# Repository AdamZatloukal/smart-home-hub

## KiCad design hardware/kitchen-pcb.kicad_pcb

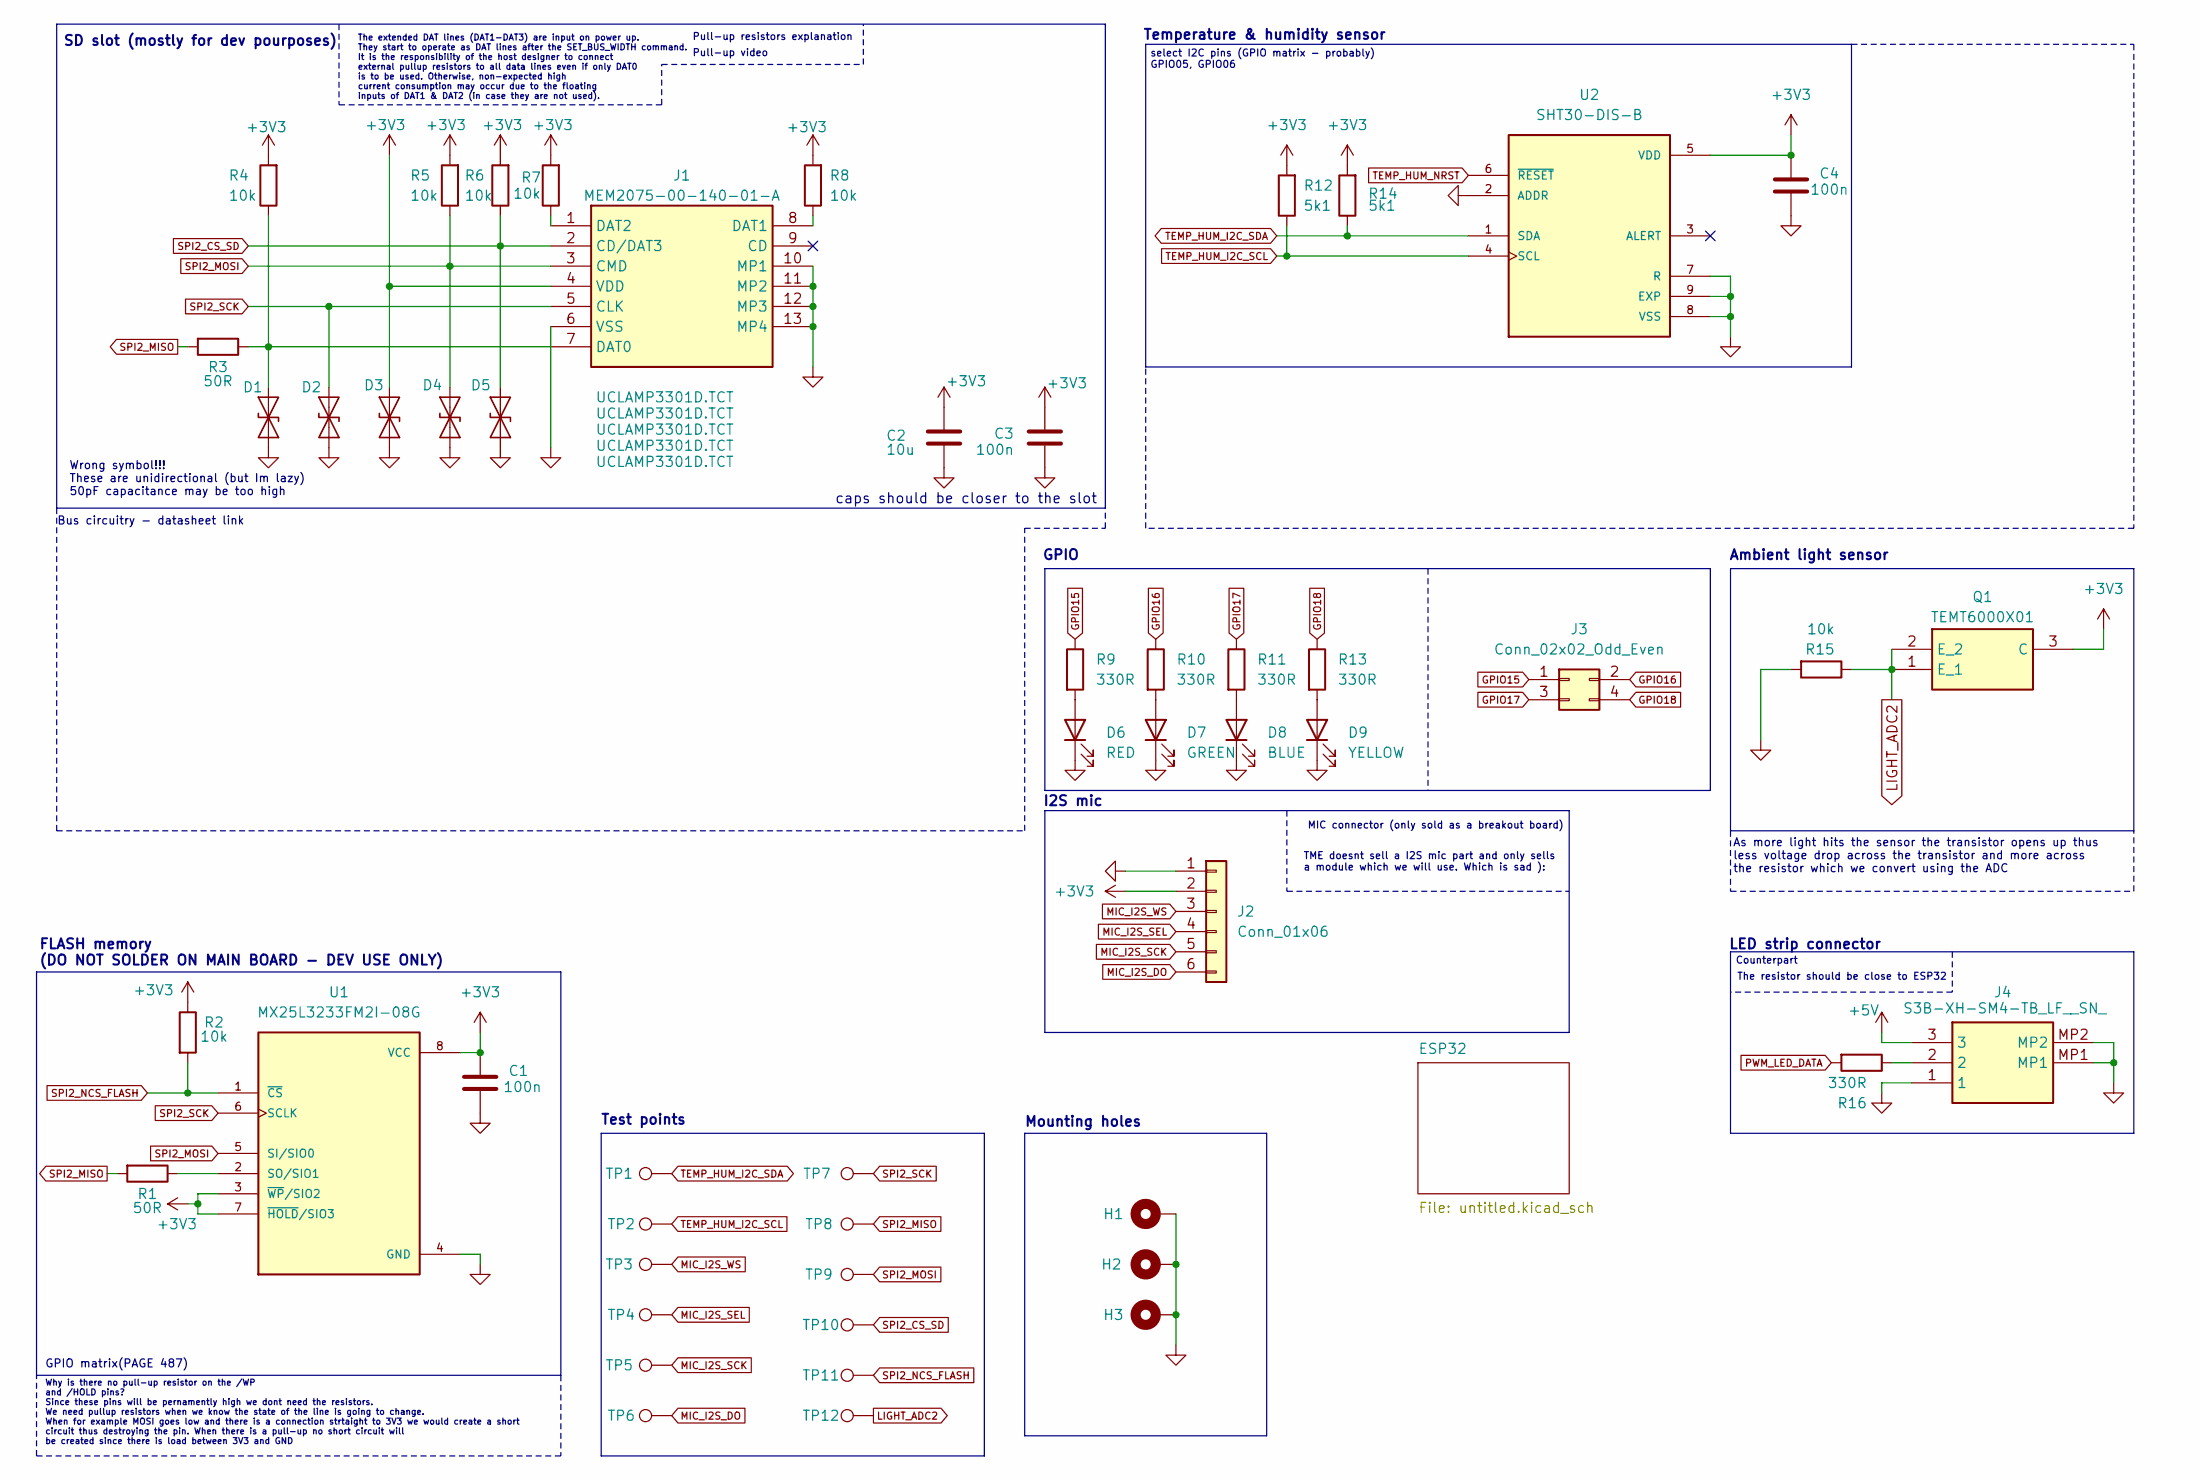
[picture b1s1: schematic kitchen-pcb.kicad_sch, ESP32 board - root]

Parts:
C1, C3, C4: 100n; C_0805_2012Metric_Pad1.18x1.45mm_HandSolder
C2: 10u; C_0805_2012Metric_Pad1.18x1.45mm_HandSolder
D1, D2, D3, D4, D5: UCLAMP3301D.TCT; SOD2512X110L
D6: RED; LED_0603_1608Metric_Pad1.05x0.95mm_HandSolder
D7: GREEN; LED_0603_1608Metric_Pad1.05x0.95mm_HandSolder
D8: BLUE; LED_0603_1608Metric_Pad1.05x0.95mm_HandSolder
D9: YELLOW; LED_0603_1608Metric_Pad1.05x0.95mm_HandSolder
H1, H2, H3: MountingHole_Pad; MountingHole_3.2mm_M3_DIN965_Pad_TopBottom
J1: MEM2075-00-140-01-A; MEM20750014001A; Manufacturer_Part_Number MEM2075-00-140-01-A
J2: Conn_01x06; mic-module
J3: Conn_02x02_Odd_Even; PinHeader_2x02_P2.54mm_Vertical
J4: S3B-XH-SM4-TB_LF__SN_; S3BXHSM4TBLFSN; Mouser Part Number N/A
Q1: TEMT6000X01; Manufacturer_Part_Number TEMT6000X01
R1, R3: 50R; R_0603_1608Metric_Pad0.98x0.95mm_HandSolder
R2, R4, R5, R6, R7, R8, R15: 10k; R_0805_2012Metric_Pad1.20x1.40mm_HandSolder
R9, R10, R11, R13, R16: 330R; R_0805_2012Metric_Pad1.20x1.40mm_HandSolder
R12, R14: 5k1; R_0805_2012Metric_Pad1.20x1.40mm_HandSolder
TP1, TP3, TP7: Test_SCK; TestPoint_Pad_D1.0mm
TP2, TP4, TP8: Test_MISO; TestPoint_Pad_D1.0mm
TP5, TP9: Test_MOSI; TestPoint_Pad_D1.0mm
TP6, TP10: Test_CS_SD; TestPoint_Pad_D1.0mm
TP11, TP12: Test_NCS_FLASH; TestPoint_Pad_D1.0mm
U1: MX25L3233FM2I-08G; SOIC127P790X216-8N_MX25L3233FM2I-08G; PARTREV 1.6
U2: SHT30-DIS-B; DFN250X250X100-9N

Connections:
+3V3: C1.2, C2.1, C3.1, C4.2, D3.2 (A2), J1.4 (VDD), J2.2, Q1.3 (C), R2.1, R4.2, R5.2, R6.2, R7.2, R8.2, R12.2, R14.2, U1.3 (~WP/SIO2), U1.7 (~HOLD/SIO3), U1.8 (VCC), U2.5 (VDD); also elsewhere on the board
+5V: J4.3; also elsewhere on the board
GND: C1.1, C2.2, C3.2, C4.1, D1.1 (A1), D2.1 (A1), D3.1 (A1), D4.1 (A1), D5.1 (A1), D6.1 (K), D7.1 (K), D8.1 (K), D9.1 (K), H1.1, H2.1, H3.1, J1.6 (VSS), J1.10 (MP1), J1.11 (MP2), J1.12 (MP3), J1.13 (MP4), J2.1, J4.1, J4.MP1, J4.MP2, R15.2, U1.4 (GND), U2.2 (ADDR), U2.7 (R), U2.8 (VSS), U2.9 (EXP); also elsewhere on the board
GPIO15: J3.1, R9.1; also elsewhere on the board
GPIO16: J3.2, R10.1; also elsewhere on the board
GPIO17: J3.3, R11.1; also elsewhere on the board
GPIO18: J3.4, R13.1; also elsewhere on the board
LIGHT_ADC2: Q1.1 (E_1), Q1.2 (E_2), R15.1, TP12.1; also elsewhere on the board
MIC_I2S_DO: J2.6, TP6.1; also elsewhere on the board
MIC_I2S_SCK: J2.5, TP5.1; also elsewhere on the board
MIC_I2S_SEL: J2.4, TP4.1; also elsewhere on the board
MIC_I2S_WS: J2.3, TP3.1; also elsewhere on the board
unnamed: D1.2 (A2), J1.7 (DAT0), R3.1, R4.1
unnamed: D6.2 (A), R9.2
unnamed: D7.2 (A), R10.2
unnamed: D8.2 (A), R11.2
unnamed: D9.2 (A), R13.2
unnamed: J1.8 (DAT1), R8.1
unnamed: J1.1 (DAT2), R7.1
unnamed: J4.2, R16.1
unnamed: R1.1, U1.2 (SO/SIO1)
PWM_LED_DATA: R16.2; also elsewhere on the board
SPI2_CS_SD: D5.2 (A2), J1.2 (CD/DAT3), R6.1, TP10.1; also elsewhere on the board
SPI2_MISO: R1.2, R3.2, TP8.1; also elsewhere on the board
SPI2_MOSI: D4.2 (A2), J1.3 (CMD), R5.1, TP9.1, U1.5 (SI/SIO0); also elsewhere on the board
SPI2_NCS_FLASH: R2.2, TP11.1, U1.1 (~CS); also elsewhere on the board
SPI2_SCK: D2.2 (A2), J1.5 (CLK), TP7.1, U1.6 (SCLK); also elsewhere on the board
TEMP_HUM_I2C_SCL: R12.1, TP2.1, U2.4 (SCL); also elsewhere on the board
TEMP_HUM_I2C_SDA: R14.1, TP1.1, U2.1 (SDA); also elsewhere on the board
TEMP_HUM_NRST: U2.6 (~RESET); also elsewhere on the board

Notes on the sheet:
Pull-up resistors explanation
As more light hits the sensor the transistor opens up thus less voltage drop across the transistor and more across the resistor which we convert using the ADC
Ambient light sensor
Mounting holes
MIC connector (only sold as a breakout board)
Counterpart
caps should be closer to the slot
Bus circuitry - datasheet link
Why is there no pull-up resistor on the /WP and /HOLD pins? Since these pins will be pernamently high we dont need the resistors. We need pullup resistors when we know the state of the line is going to change. When for example MOSI goes low and there is a connection strtaight to 3V3 we would create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
Wrong symbol!!! These are unidirectional (but Im lazy) 50pF capacitance may be too high
GPIO matrix(PAGE 487)
Pull-up video
GPIO
FLASH memory (DO NOT SOLDER ON MAIN BOARD - DEV USE ONLY)
SD slot (mostly for dev pourposes)
LED strip connector
TME doesnt sell a I2S mic part and only sells a module which we will use. Which is sad ):
Test points
The extended DAT lines (DAT1-DAT3) are input on power up. They start to operate as DAT lines after the SET_BUS_WIDTH command. It is the responsibility of the host designer to connect external pullup resistors to all data lines even if only DAT0 is to be used. Otherwise, non-expected high current co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
Temperature & humidity sensor
I2S mic
The resistor should be close to ESP32
select I2C pins (GPIO matrix - probably) GPIO05, GPIO06

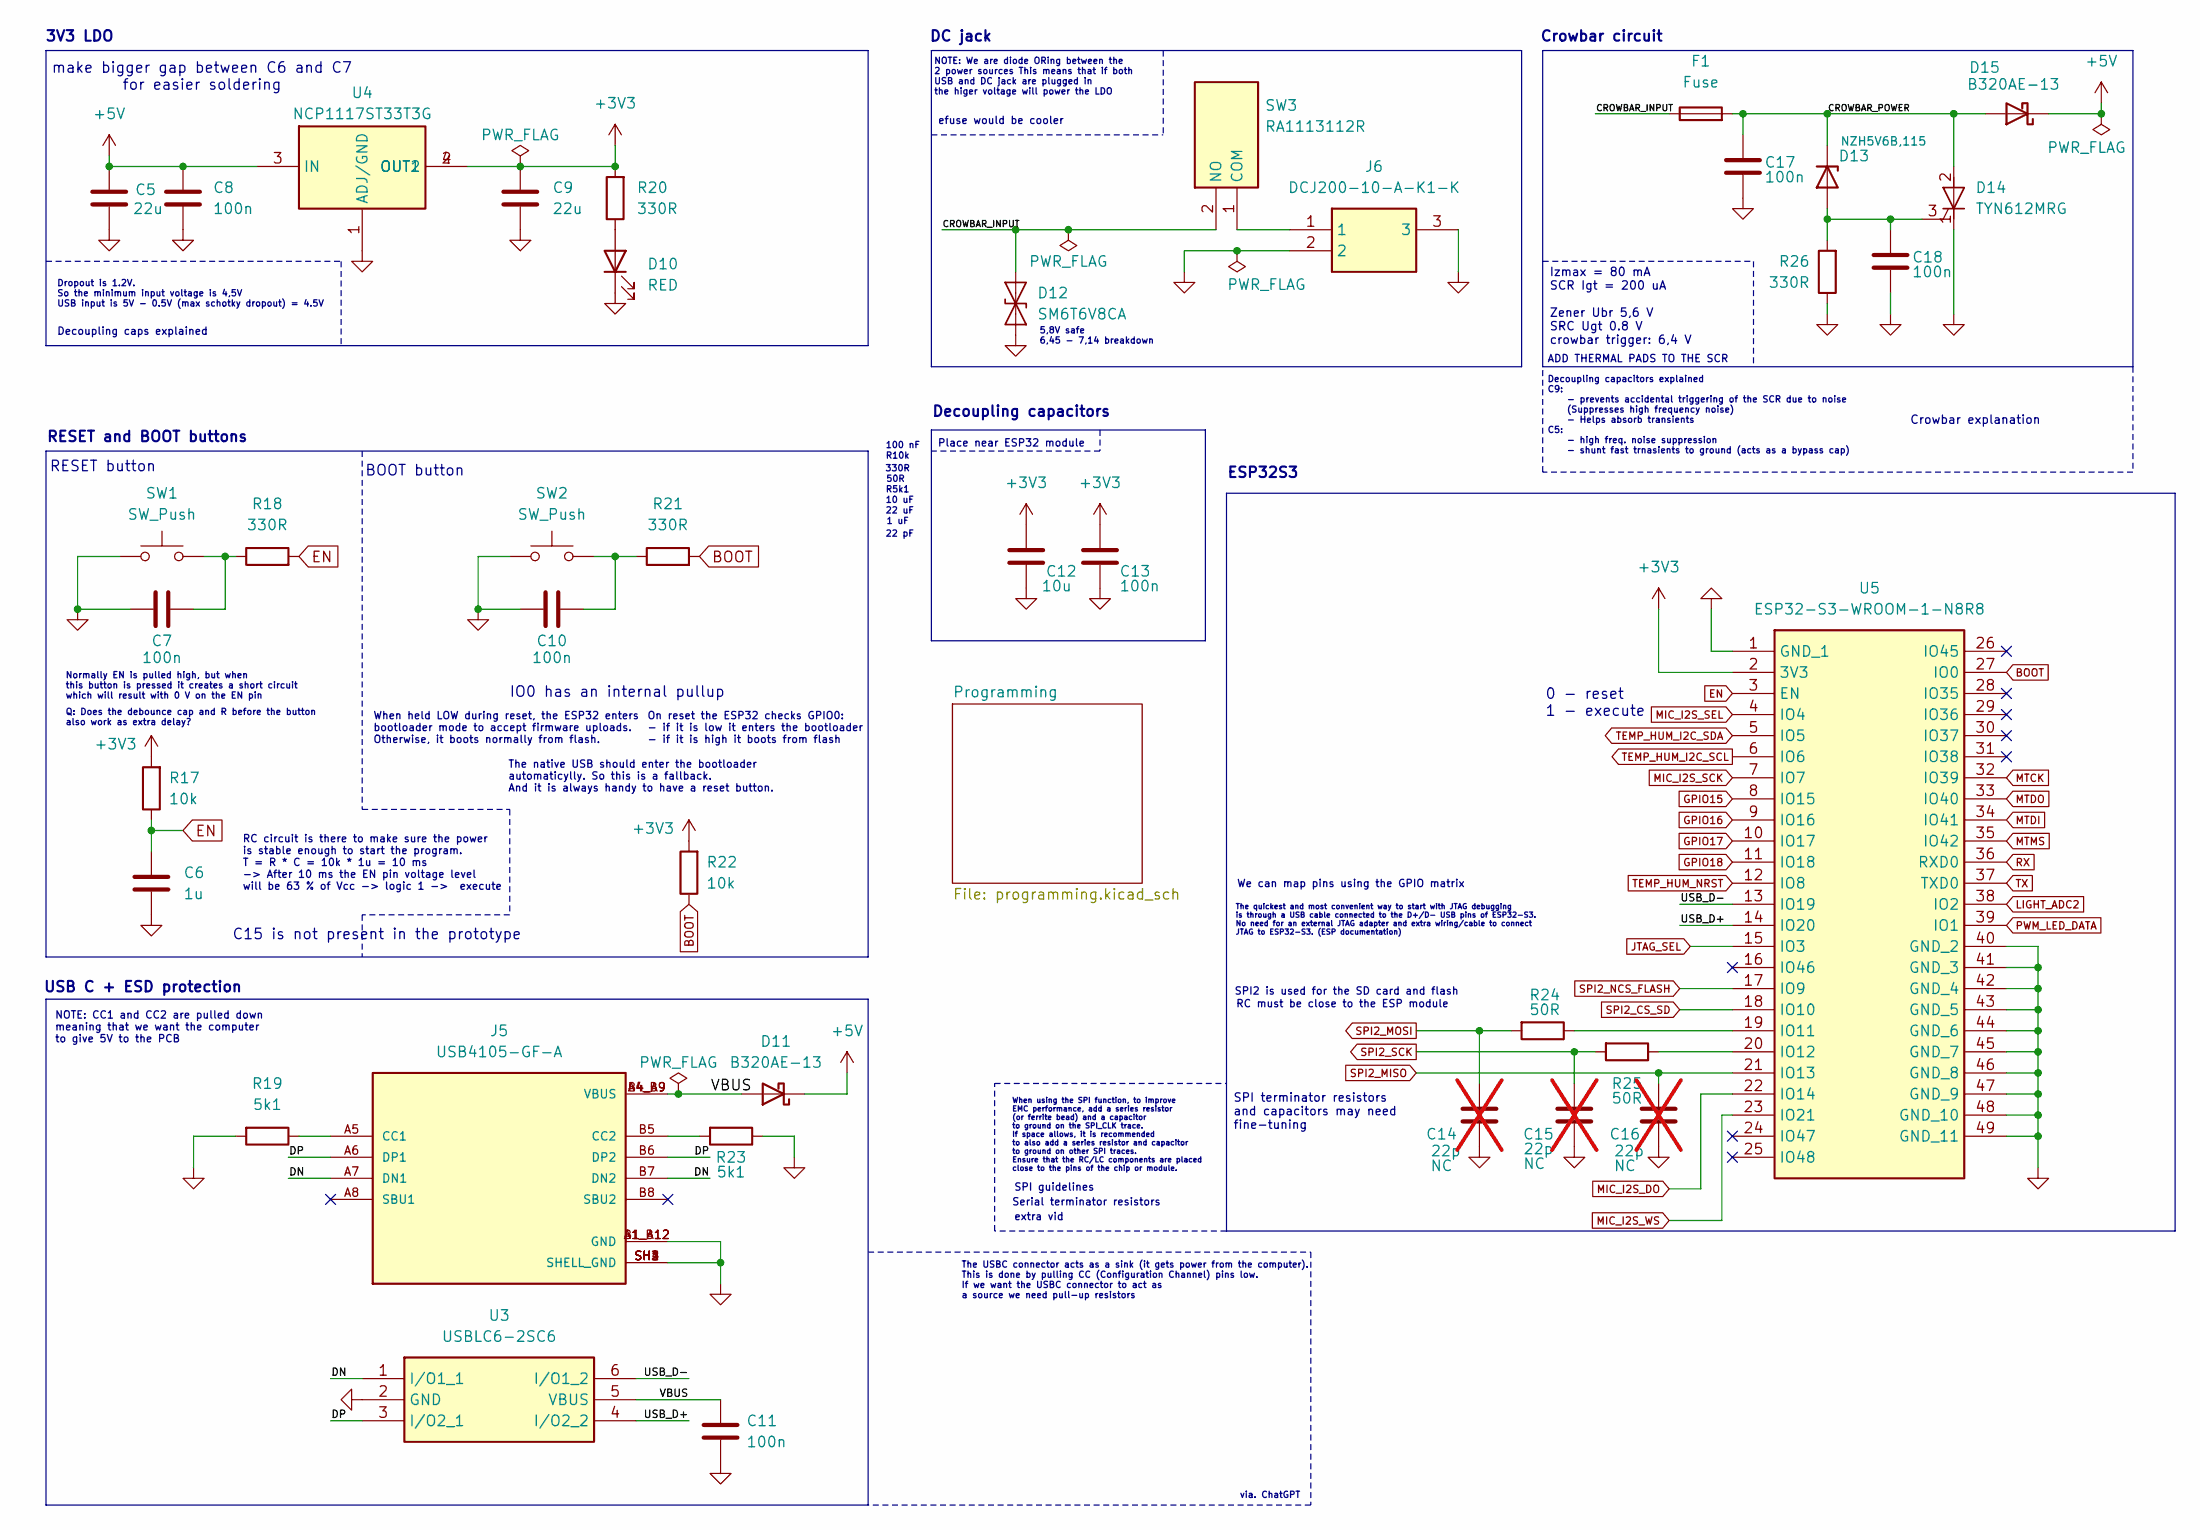
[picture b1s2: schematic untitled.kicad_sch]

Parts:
C5, C9: 22u; C_0805_2012Metric_Pad1.18x1.45mm_HandSolder
C6: 1u; C_0805_2012Metric_Pad1.18x1.45mm_HandSolder
C7, C8, C10, C11, C13, C17, C18: 100n; C_0805_2012Metric_Pad1.18x1.45mm_HandSolder
C12: 10u; C_0805_2012Metric_Pad1.18x1.45mm_HandSolder
C14, C15, C16: 22p; C_0805_2012Metric_Pad1.18x1.45mm_HandSolder; not fitted
D10: RED; LED_0603_1608Metric_Pad1.05x0.95mm_HandSolder
D11: B320AE-13; DIONM5226X230N
D12: SM6T6V8CA; DIONM5436X265N
D13: NZH5V6B,115; D_SOD-123F
D14: TYN612MRG; TS820600B
D15: B320AE-13; D_SMA
F1: Fuse; FUSC6125X279N
J5: USB4105-GF-A; GCT_USB4105-GF-A; PARTREV B4
J6: DCJ200-10-A-K1-K; BarrelJack_GCT_DCJ200-10-A_Horizontal; Manufacturer_Part_Number DCJ200-10-A-K1-K
R17, R22: 10k; R_0805_2012Metric_Pad1.20x1.40mm_HandSolder
R18, R20, R21, R26: 330R; R_0805_2012Metric_Pad1.20x1.40mm_HandSolder
R19, R23: 5k1; R_0805_2012Metric_Pad1.20x1.40mm_HandSolder
R24, R25: 50R; R_0402_1005Metric_Pad0.72x0.64mm_HandSolder
SW1, SW2: SW_Push; SW_PUSH_6mm_H9.5mm
SW3: RA1113112R; Manufacturer_Part_Number R1966ABLKBLKGR
U3: USBLC6-2SC6; SOT95P280X145-6N; Manufacturer_Part_Number USBLC6-2SC6
U4: NCP1117ST33T3G; SOT230P700X180-4N
U5: ESP32-S3-WROOM-1-N8R8; ESP32S3WROOM1N4; Manufacturer_Part_Number ESP32-S3-WROOM-1-N8R8

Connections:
+3V3: C9.1, C12.1, C13.1, R17.2, R20.2, R22.2, U4.2 (OUT1), U4.4 (OUT2), U5.2 (3V3); also elsewhere on the board
+5V: C5.1, C8.1, D11.1 (K), D15.1 (K), U4.3 (IN); also elsewhere on the board
/ESP32/CROWBAR_INPUT: D12.2 (A2), F1.1, SW3.2 (NO)
/ESP32/CROWBAR_POWER: C17.1, D13.1 (K), D14.2 (A), D15.2 (A), F1.2
/ESP32/DN: J5.A7 (DN1), J5.B7 (DN2), U3.1 (I/O1_1)
/ESP32/DP: J5.A6 (DP1), J5.B6 (DP2), U3.3 (I/O2_1)
/ESP32/USB_D+: U3.4 (I/O2_2), U5.14 (IO20)
/ESP32/USB_D-: U3.6 (I/O1_2), U5.13 (IO19)
/ESP32/VBUS: C11.1, D11.2 (A), J5.A4_B9 (VBUS), J5.B4_A9 (VBUS), U3.5 (VBUS)
BOOT: R21.2, R22.1, U5.27 (IO0); also elsewhere on the board
EN: C6.2, R17.1, R18.2, U5.3 (EN); also elsewhere on the board
GND: C5.2, C6.1, C7.1, C8.2, C9.2, C10.1, C11.2, C12.2, C13.2, C14.1, C15.1, C16.1, C17.2, C18.2, D10.1 (K), D12.1 (A1), D14.1 (K), J5.A1_B12 (GND), J5.B1_A12 (GND), J5.SH1 (SHELL_GND), J5.SH2 (SHELL_GND), J5.SH3 (SHELL_GND), J5.SH4 (SHELL_GND), J6.2, J6.3, R19.2, R23.1, R26.1, SW1.1, SW2.1, U3.2 (GND), U4.1 (ADJ/GND), U5.1 (GND_1), U5.40 (GND_2), U5.41 (GND_3), U5.42 (GND_4), U5.43 (GND_5), U5.44 (GND_6), U5.45 (GND_7), U5.46 (GND_8), U5.47 (GND_9), U5.48 (GND_10), U5.49 (GND_11); also elsewhere on the board
GPIO15: U5.8 (IO15); also elsewhere on the board
GPIO16: U5.9 (IO16); also elsewhere on the board
GPIO17: U5.10 (IO17); also elsewhere on the board
GPIO18: U5.11 (IO18); also elsewhere on the board
JTAG_SEL: U5.15 (IO3); also elsewhere on the board
LIGHT_ADC2: U5.38 (IO2); also elsewhere on the board
MIC_I2S_DO: U5.22 (IO14); also elsewhere on the board
MIC_I2S_SCK: U5.7 (IO7); also elsewhere on the board
MIC_I2S_SEL: U5.4 (IO4); also elsewhere on the board
MIC_I2S_WS: U5.23 (IO21); also elsewhere on the board
MTCK: U5.32 (IO39); also elsewhere on the board
MTDI: U5.34 (IO41); also elsewhere on the board
MTDO: U5.33 (IO40); also elsewhere on the board
MTMS: U5.35 (IO42); also elsewhere on the board
unnamed: C7.2, R18.1, SW1.2
unnamed: C10.2, R21.1, SW2.2
unnamed: D10.2 (A), R20.1
unnamed: C18.1, D13.2 (A), D14.3 (G), R26.2
unnamed: J5.A5 (CC1), R19.1
unnamed: J5.B5 (CC2), R23.2
unnamed: J6.1, SW3.1 (COM)
unnamed: R24.1, U5.19 (IO11)
unnamed: R25.1, U5.20 (IO12)
PWM_LED_DATA: U5.39 (IO1); also elsewhere on the board
RX: U5.36 (RXD0); also elsewhere on the board
SPI2_CS_SD: U5.18 (IO10); also elsewhere on the board
SPI2_MISO: C16.2, U5.21 (IO13); also elsewhere on the board
SPI2_MOSI: C14.2, R24.2; also elsewhere on the board
SPI2_NCS_FLASH: U5.17 (IO9); also elsewhere on the board
SPI2_SCK: C15.2, R25.2; also elsewhere on the board
TEMP_HUM_I2C_SCL: U5.6 (IO6); also elsewhere on the board
TEMP_HUM_I2C_SDA: U5.5 (IO5); also elsewhere on the board
TEMP_HUM_NRST: U5.12 (IO8); also elsewhere on the board
TX: U5.37 (TXD0); also elsewhere on the board

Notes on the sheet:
330R
Q: Does the debounce cap and R before the button also work as extra delay?
DC jack
USB C + ESD protection
3V3 LDO
NOTE: CC1 and CC2 are pulled down meaning that we want the computer to give 5V to the PCB
Crowbar explanation
Serial terminator resistors
R5k1
22 uF
Decoupling capacitors explained C9: - prevents accidental triggering of the SCR due to noise (Suppresses high frequency noise) - Helps absorb transients C5: - high freq. noise suppression - shunt fast trnasients to ground (acts as a bypass cap)
R10k
SPI terminator resistors and capacitors may need fine-tuning
We can map pins using the GPIO matrix
0 - reset 1 - execute
ADD THERMAL PADS TO THE SCR
100 nF
RESET button
When held LOW during reset, the ESP32 enters bootloader mode to accept firmware uploads. Otherwise, it boots normally from flash.
SPI guidelines
IO0 has an internal pullup
make bigger gap between C6 and C7 for easier soldering
The USBC connector acts as a sink (it gets power from the computer). This is done by pulling CC (Configuration Channel) pins low. If we want the USBC connector to act as a source we need pull-up resistors
Decoupling caps explained
Izmax = 80 mA SCR Igt = 200 uA Zener Ubr 5,6 V SRC Ugt 0.8 V crowbar trigger: 6,4 V
Place near ESP32 module
50R
The quickest and most convenient way to start with JTAG debugging is through a USB cable connected to the D+/D- USB pins of ESP32-S3. No need for an external JTAG adapter and extra wiring/cable to connect JTAG to ESP32-S3. (ESP documentation)
extra vid
Crowbar circuit
efuse would be cooler
Dropout is 1.2V. So the minimum input voltage is 4,5V USB input is 5V - 0.5V (max schotky dropout) = 4.5V
RESET and BOOT buttons
22 pF
10 uF
via. ChatGPT
SPI2 is used for the SD card and flash
Decoupling capacitors
RC circuit is there to make sure the power is stable enough to start the program. T = R * C = 10k * 1u = 10 ms -> After 10 ms the EN pin voltage level will be 63 % of Vcc -> logic 1 -> execute
5,8V safe 6,45 - 7,14 breakdown

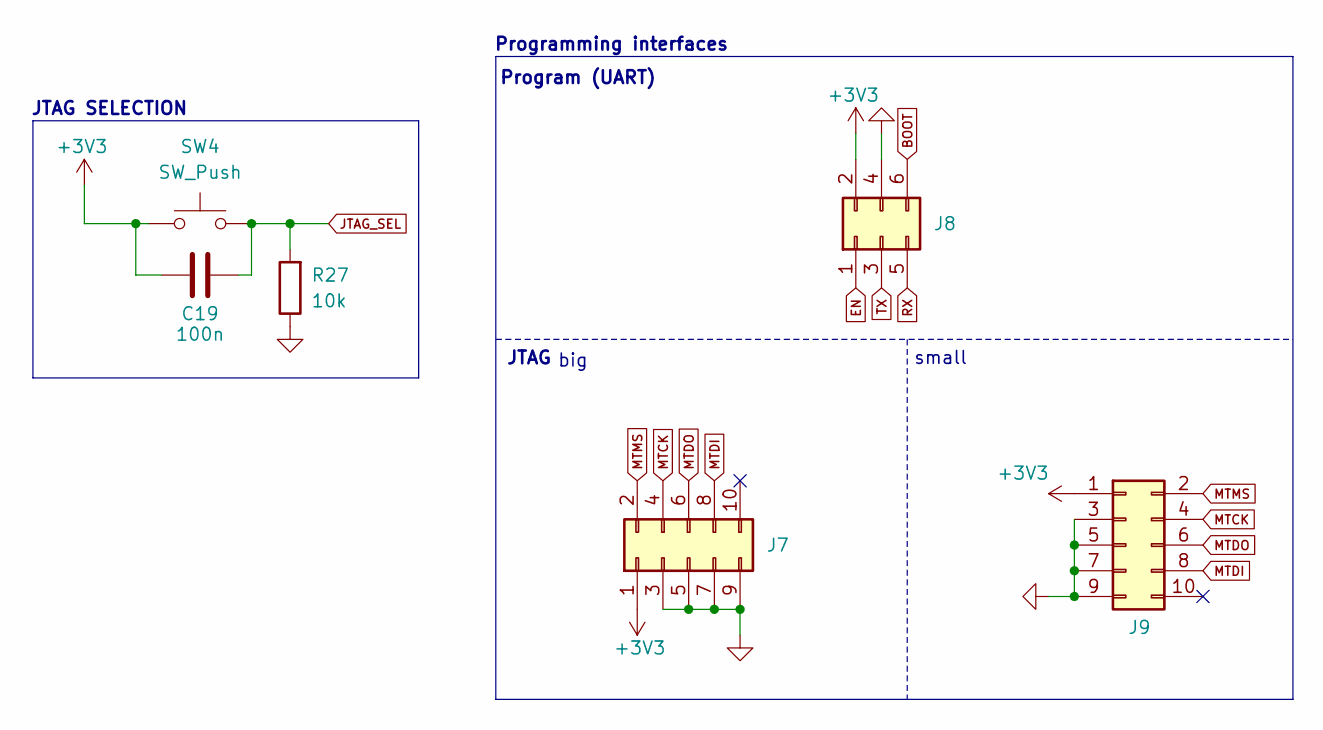
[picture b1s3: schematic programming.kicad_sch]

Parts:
C19: 100n; C_0805_2012Metric_Pad1.18x1.45mm_HandSolder
J7: Conn_02x05_Odd_Even; PinHeader_2x05_P2.54mm_Vertical
J8: Conn_02x03_Odd_Even; PinHeader_2x03_P2.54mm_Vertical
J9: Conn_02x05_Odd_Even; FTSH10501LDVK
R27: 10k; R_0805_2012Metric_Pad1.20x1.40mm_HandSolder
SW4: SW_Push; SW_PUSH_6mm_H9.5mm

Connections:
+3V3: C19.1, J7.1, J8.2, J9.1, SW4.1; also elsewhere on the board
BOOT: J8.6; also elsewhere on the board
EN: J8.1; also elsewhere on the board
GND: J7.3, J7.5, J7.7, J7.9, J8.4, J9.3, J9.5, J9.7, J9.9, R27.1; also elsewhere on the board
JTAG_SEL: C19.2, R27.2, SW4.2; also elsewhere on the board
MTCK: J7.4, J9.4; also elsewhere on the board
MTDI: J7.8, J9.8; also elsewhere on the board
MTDO: J7.6, J9.6; also elsewhere on the board
MTMS: J7.2, J9.2; also elsewhere on the board
RX: J8.5; also elsewhere on the board
TX: J8.3; also elsewhere on the board

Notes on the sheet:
JTAG
big
Programming interfaces
Program (UART)
small
JTAG SELECTION

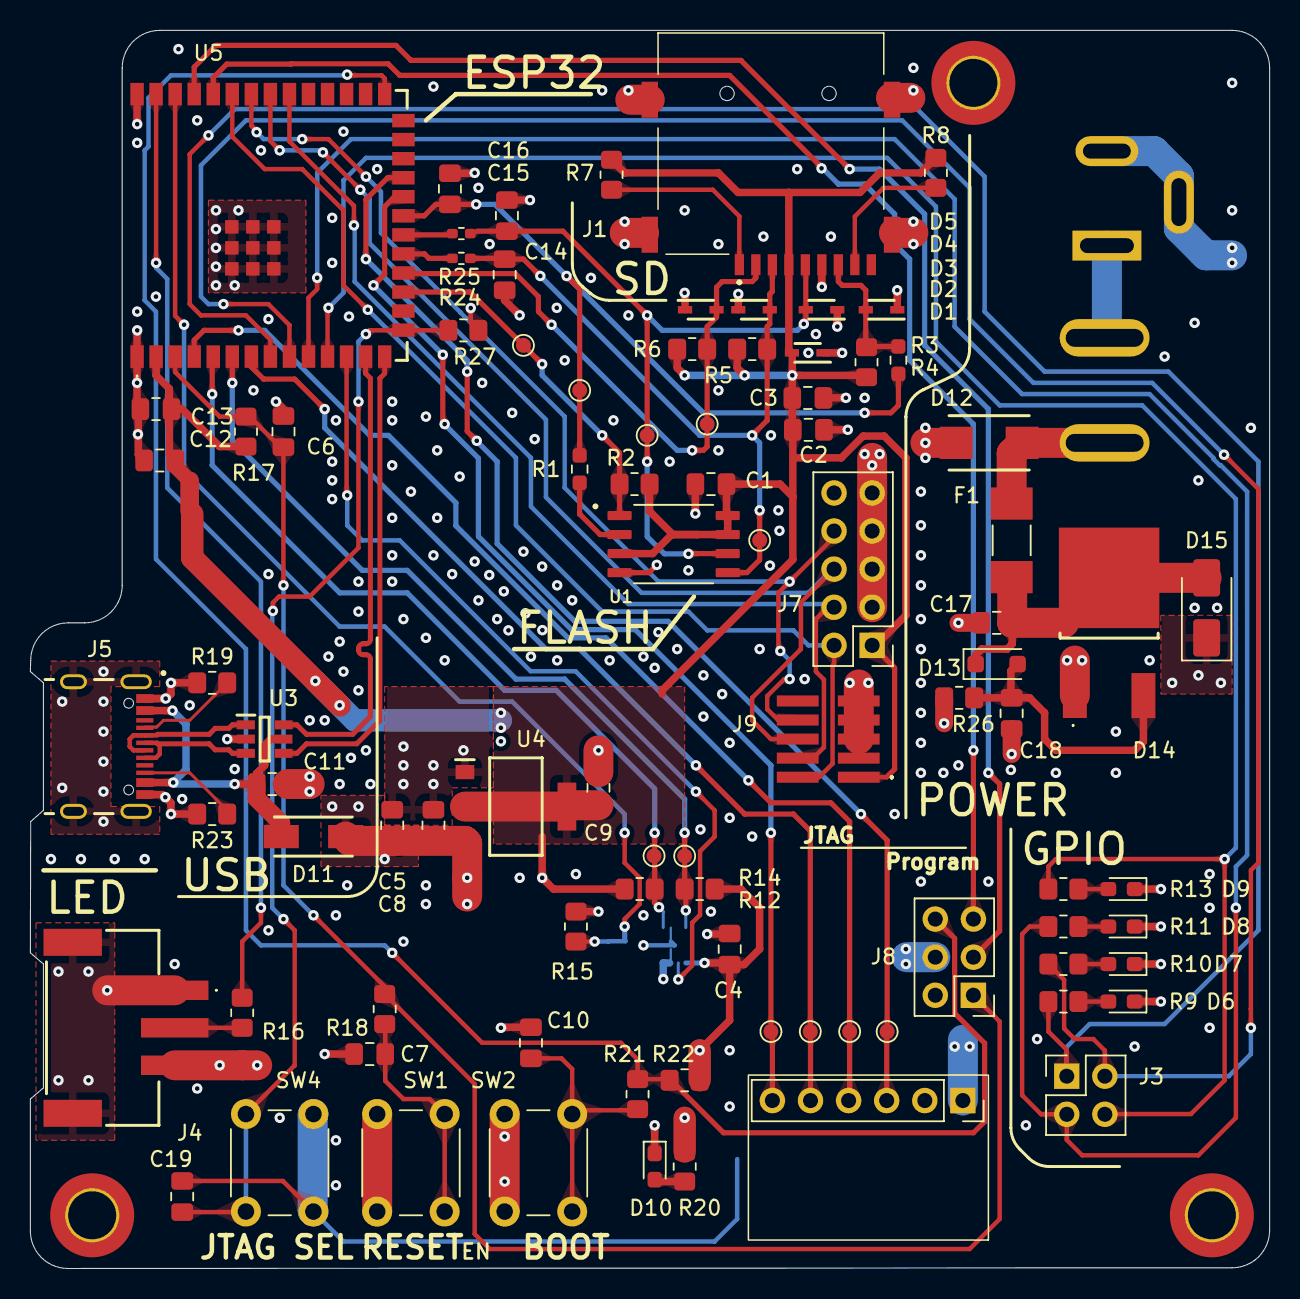
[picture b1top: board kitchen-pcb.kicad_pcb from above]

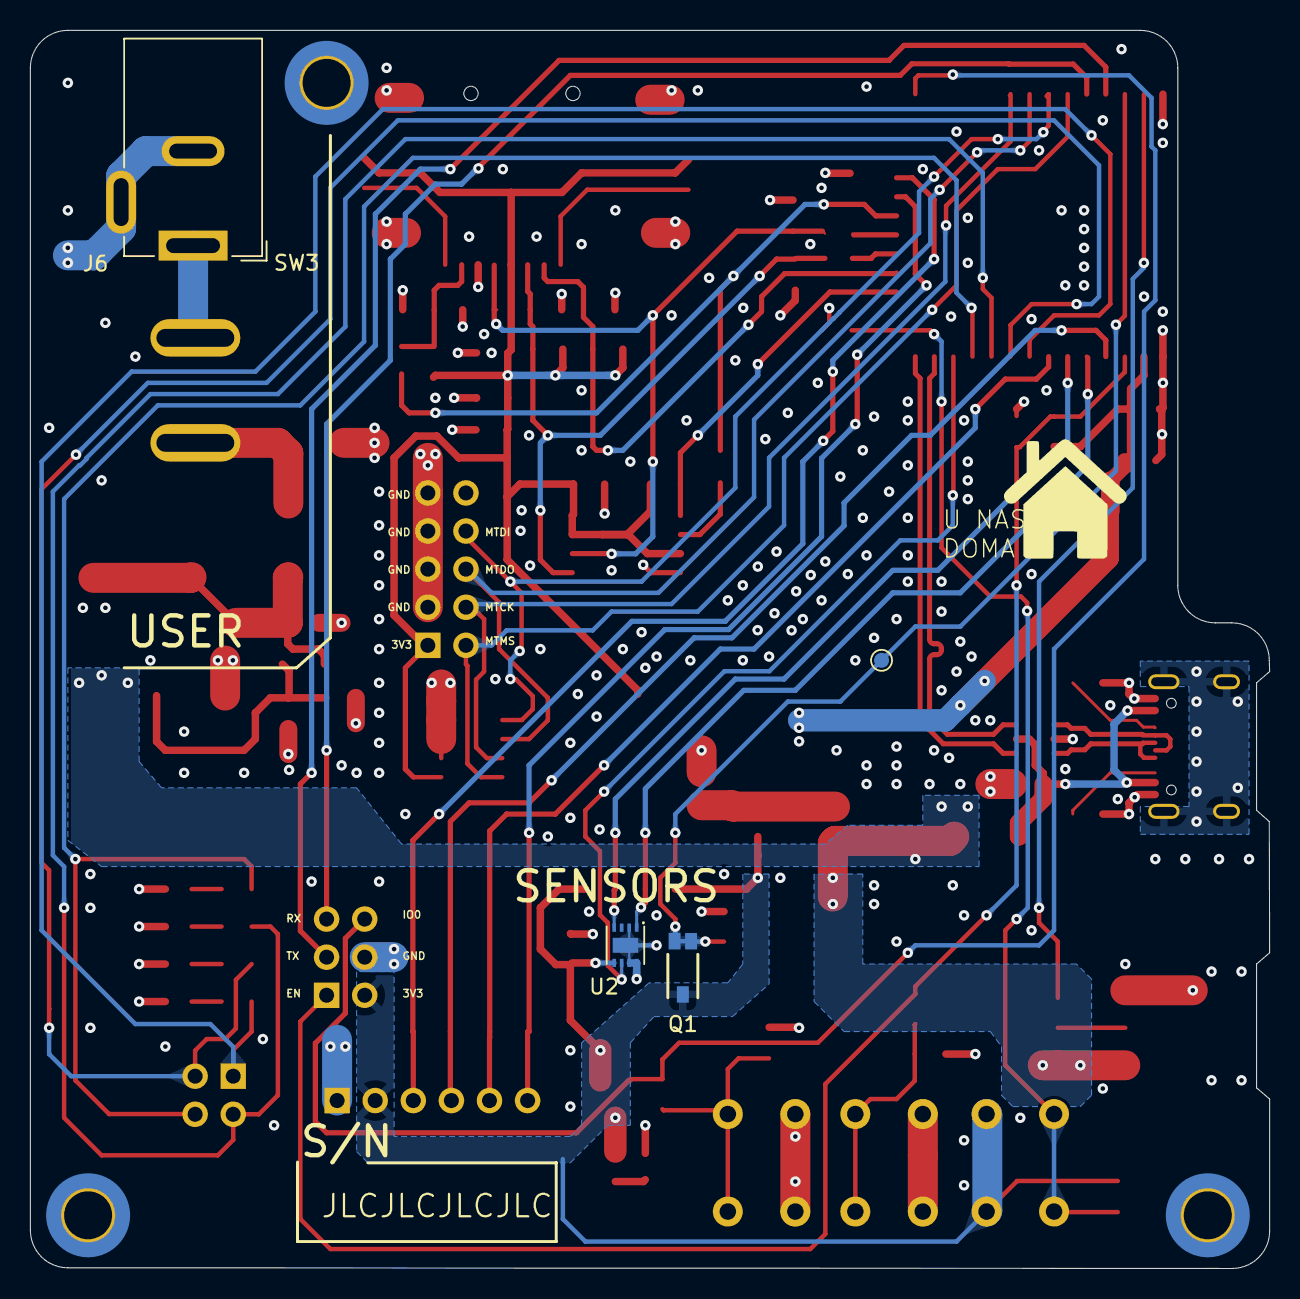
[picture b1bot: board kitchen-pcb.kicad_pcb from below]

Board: 4 copper layers, 82.6 x 82.5 mm, 96 parts (5 on the bottom side), 55 nets.

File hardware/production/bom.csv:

Designator,Footprint,Quantity,Value,LCSC Part #
"C1, C10, C11, C13, C17, C18, C19, C3, C4, C7, C8",0805,11,100n,
"C12, C2",0805,2,10u,
"C14, C15, C16",0805,3,22p,
"C5, C9",0805,2,22u,
C6,0805,1,1u,
"D1, D2, D3, D4, D5",SOD2512X110L,5,UCLAMP3301D.TCT,
"D10, D6",0603,2,RED,
D11,DIONM5226X230N,1,B320AE-13,
D12,DIONM5436X265N,1,SM6T6V8CA,
D13,D_SOD-123F,1,"NZH5V6B,115",
D14,TS820600B,1,TYN612MRG,
D15,D_SMA,1,B320AE-13,
D7,0603,1,GREEN,
D8,0603,1,BLUE,
D9,0603,1,YELLOW,
F1,FUSC6125X279N,1,Fuse,
J1,MEM20750014001A,1,MEM2075-00-140-01-A,
J2,mic-module,1,Conn_01x06,
J3,PinHeader_2x02_P2.54mm_Vertical,1,Conn_02x02_Odd_Even,
J4,S3BXHSM4TBLFSN,1,S3B-XH-SM4-TB_LF__SN_,
J5,GCT_USB4105-GF-A,1,USB4105-GF-A,
J6,BarrelJack_GCT_DCJ200-10-A_Horizontal,1,DCJ200-10-A-K1-K,
J7,PinHeader_2x05_P2.54mm_Vertical,1,Conn_02x05_Odd_Even,
J8,PinHeader_2x03_P2.54mm_Vertical,1,Conn_02x03_Odd_Even,
J9,FTSH10501LDVK,1,Conn_02x05_Odd_Even,
Q1,TEMT6000X01,1,TEMT6000X01,
"R1, R3",0603,2,50R,
"R10, R11, R13, R16, R18, R20, R21, R26, R9",0805,9,330R,
"R12, R14, R19, R23",0805,4,5k1,
"R15, R17, R2, R22, R27, R4, R5, R6, R7, R8",0805,10,10k,
"R24, R25",0402,2,50R,
"SW1, SW2, SW4",SW_PUSH_6mm_H9.5mm,3,SW_Push,
SW3,RA1113112R,1,RA1113112R,
"TP1, TP3, TP7",TestPoint_Pad_D1.0mm,3,Test_SCK,
"TP10, TP6",TestPoint_Pad_D1.0mm,2,Test_CS_SD,
"TP11, TP12",TestPoint_Pad_D1.0mm,2,Test_NCS_FLASH,
"TP2, TP4, TP8",TestPoint_Pad_D1.0mm,3,Test_MISO,
"TP5, TP9",TestPoint_Pad_D1.0mm,2,Test_MOSI,
U1,SOIC127P790X216-8N_MX25L3233FM2I-08G,1,MX25L3233FM2I-08G,
U2,DFN250X250X100-9N,1,SHT30-DIS-B,
U3,SOT95P280X145-6N,1,USBLC6-2SC6,
U4,SOT230P700X180-4N,1,NCP1117ST33T3G,
U5,ESP32S3WROOM1N4,1,ESP32-S3-WROOM-1-N8R8,

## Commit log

2025-07-22 Layout v0.2
2025-07-22 Layout v0.3
2025-07-23 Schematics adjustments - updated some components
2025-07-26 Added notes to schematics, SPI modifications
2025-07-27 Layout v0,4
2025-07-27 Layout v0.5
2025-07-28 Changed to microSD, layout v0.6.1
2025-07-29 Layout v0.6.2, SW1 footprint
2025-07-30 SD card routing v0.1
2025-07-30 FLASH routing
2025-07-31 Error, warning free routing v0.1 (no silkscreen)
2025-08-01 DFM ready PCB no silkscreen
2025-08-02 Added silkscreen
2025-08-03 Production ready v0.1
2025-08-03 Track & via free board ready for routing
2025-08-03 PCB v0.2 (Changed GPIO routing, better power distribution)
2025-08-04 v0.3.1 Changed board stackup and impedance controlled traces
2025-08-05 v0.4 - ORDERED
2026-01-21 Working prototype, PCB prototype revision done
2026-01-21 test
2026-01-21 pcb file is broken
2026-01-21 fixed pcb file
2026-01-21 rought first draft - silkscrren, crossover problems, modify for easier soldering
2026-01-21 Tried to prevent crosstalk, fixed silkscreen, changes to fit DFM
2026-01-21 minor tweaks - sent to production
2026-01-22 wifi-test set-color command
2026-01-22 set-color + fx start
2026-01-23 added fx uri needs adjustments (but concept works)
2026-01-24 working set mode color speed brightness
2026-01-29 original i2s config for reference
2026-02-01 fixing merge conflicts
2026-02-01 esp now basic config
2026-02-01 set mac addr
2026-02-01 basic espnow setup recv
2026-02-01 espnow channel set hardcoded
2026-02-07 software first draft, disabled mic task
2026-02-07 first sw draft, disabled mic task
2026-02-07 Remove stuff
2026-02-08 fetching data, async storage for colors
2026-02-20 pcb 3d model
2026-02-24 enclosure
